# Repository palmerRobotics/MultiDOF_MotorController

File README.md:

# MultiDOF_MotorController
Code and design files for a multi-DOF (max 3) motor controller.

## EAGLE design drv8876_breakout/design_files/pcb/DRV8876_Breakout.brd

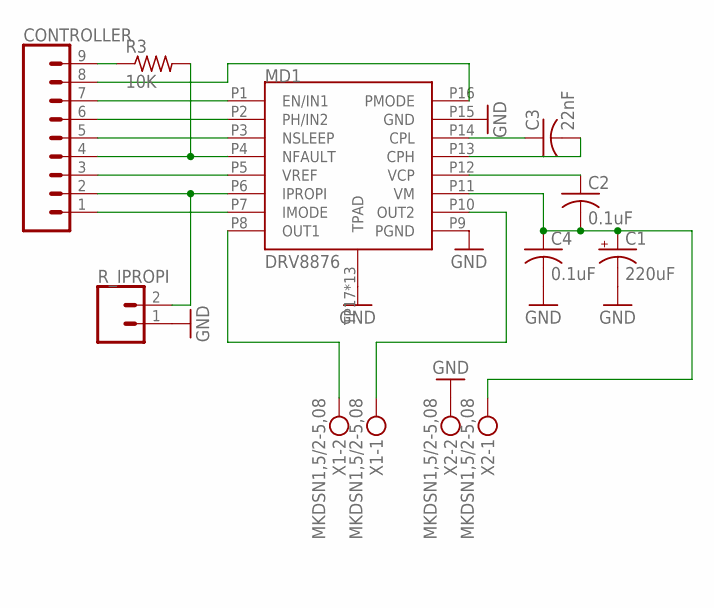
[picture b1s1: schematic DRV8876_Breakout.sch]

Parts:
C1: 220uF; E3,5-8
C2, C4: 0.1uF; C0805
C3: 22nF; C0805
CONTROLLER: CONN_09NO_SILK; 1X09_NO_SILK
MD1: DRV8876
R3: 10K; R0805
R_IPROPI: CONN_021X02_NO_SILK; 1X02_NO_SILK
X1, X2: MKDSN1,5/2-5,08

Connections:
CLP: C3.1, MD1.P14 (CPL)
CPH: C3.2, MD1.P13 (CPH)
EN/IN1: CONTROLLER.7, MD1.P1 (EN/IN1)
GND: C1.-, C4.2, MD1.P9 (PGND), MD1.P15 (GND), MD1.TP17 (TPAD), MD1.TV18 (TPAD), MD1.TV19 (TPAD), MD1.TV20 (TPAD), MD1.TV21 (TPAD), MD1.TV22 (TPAD), MD1.TV23 (TPAD), MD1.TV24 (TPAD), MD1.TV25 (TPAD), MD1.TV26 (TPAD), MD1.TV27 (TPAD), MD1.TV28 (TPAD), MD1.TV29 (TPAD), R_IPROPI.1, X2.2
IMODE: CONTROLLER.1, MD1.P7 (IMODE)
IPROPI: CONTROLLER.2, MD1.P6 (IPROPI), R_IPROPI.2
NFAULT: CONTROLLER.4, MD1.P4 (NFAULT), R3.2
NSLEEP: CONTROLLER.5, MD1.P3 (NSLEEP)
OUT1: MD1.P8 (OUT1), X1.2
OUT2: MD1.P10 (OUT2), X1.1
PH/IN2: CONTROLLER.6, MD1.P2 (PH/IN2)
PMODE: CONTROLLER.8, MD1.P16 (PMODE)
VCC: CONTROLLER.9, R3.1
VCP: C2.1, MD1.P12 (VCP)
VM: C1.+, C2.2, C4.1, MD1.P11 (VM), X2.1
VREF: CONTROLLER.3, MD1.P5 (VREF)

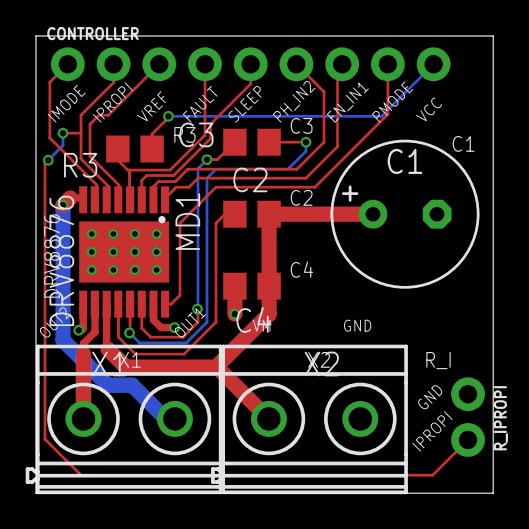
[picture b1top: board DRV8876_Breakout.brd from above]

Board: 2 copper layers, 25.4 x 25.4 mm, 10 parts (0 on the bottom side), 16 nets.

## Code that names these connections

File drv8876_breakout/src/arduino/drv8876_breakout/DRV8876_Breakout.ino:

#define ANALOG_READ_DELAY 1000 //in ms

int pmode = 12; //control mode
int en = 11; //pwm signal
int ph = 10; //direction
int nsleep = 9; //nsleep is active low (sleeps when low)
int nfault = 8; //active low
int vref = 7; //PWM freq: 980Hz, max 5.75V
int ipropi = A0; //current sensing
//tie imode to ground - don't use as output


void setup() {
  // put your setup code here, to run once:
  Serial.begin(9600);
  pinMode(pmode, OUTPUT);
  pinMode(en, OUTPUT);
  pinMode(ph, OUTPUT);
  pinMode(nsleep, OUTPUT);
  pinMode(nfault, INPUT);
  pinMode(vref, OUTPUT);
  pinMode(ipropi, INPUT);
 
  digitalWrite(pmode,LOW); //ph/en control mode
  //imode is attached to ground
  digitalWrite(nsleep, HIGH); //turn drv8876 on, pmode and imode latched
  //analogWrite(vref,255);
  digitalWrite(vref, HIGH);
  
}

void loop() {
  // put your main code here, to run repeatedly:
  digitalWrite(ph, HIGH); //forward
  Serial.println("forward");
  analogWrite(en, 128);
  delay(ANALOG_READ_DELAY);
  int Vipropi = analogRead(ipropi);
  Serial.print("ADC read:");
  Serial.println(Vipropi);
  delay(5000 - ANALOG_READ_DELAY);
  digitalWrite(ph, LOW); //reverse
  Serial.println("reverse");
  analogWrite(en, 192);
  delay(ANALOG_READ_DELAY);
  Vipropi = analogRead(ipropi);
  Serial.print("ADC read:");
  Serial.println(Vipropi);
  delay(5000 - ANALOG_READ_DELAY);  
}

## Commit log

2021-08-29 Create LICENSE
2021-11-20 Added .gitignore for future commits.
2021-11-20 Implementation of DRV8876 motor driver using a Rasberry Pi Pico. The DRV8876 breakout board has been verified to be fully functional, including current sensing & limiting capabilities.
2021-12-02 Added docs and data directories. Added IIR filter test data. Modified comments in code to increase readability.
2021-12-04 Modified .gitignore to ignore unwanted MATLAB and EAGLE files in future commits.
2021-12-04 Big commit. Added MATLAB IIR filter and EAGLE PCB design files. Added initial prototype arduino driver code verifying breakout board functionality. Added various test data. Reorganized file system fo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

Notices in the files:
parts and their libraries:
SparkFun-Connectors: Licensing: Creative Commons ShareAlike 4.0 International - https://creativecommons.org/licenses/by-sa/4.0
